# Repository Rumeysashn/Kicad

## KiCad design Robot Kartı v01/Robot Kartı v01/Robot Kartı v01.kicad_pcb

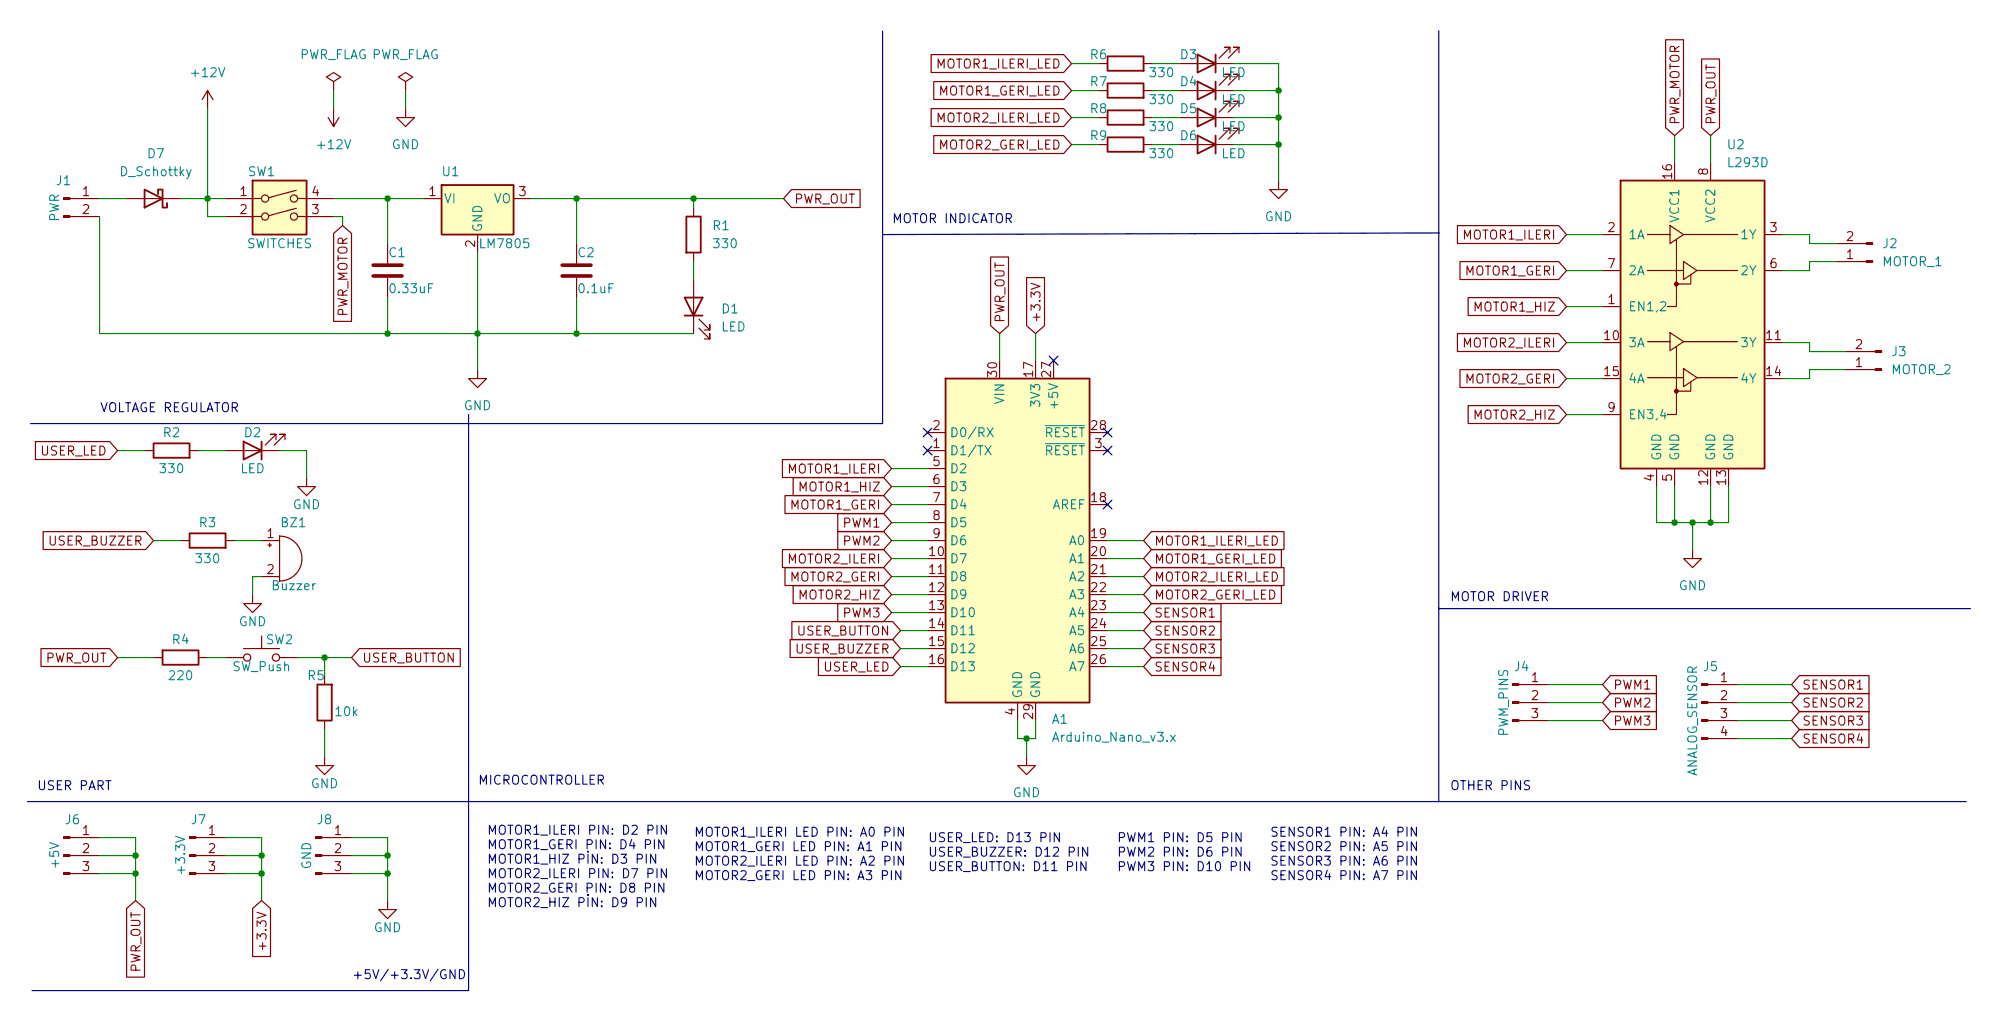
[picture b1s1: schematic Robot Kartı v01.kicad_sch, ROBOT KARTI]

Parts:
A1: Arduino_Nano_v3.x; Arduino_Nano
BZ1: Buzzer; Buzzer_12x9.5RM7.6
C1: 0.33uF; C_Disc_D3.0mm_W2.0mm_P2.50mm
C2: 0.1uF; C_Disc_D3.0mm_W2.0mm_P2.50mm
D1, D2, D3, D4, D5, D6: LED; LED_D3.0mm
D7: D_Schottky; D_A-405_P2.54mm_Vertical_AnodeUp
J1: PWR; Molex_KK-254_AE-6410-02A_1x02_P2.54mm_Vertical
J2: MOTOR_1; Molex_KK-254_AE-6410-02A_1x02_P2.54mm_Vertical
J3: MOTOR_2; Molex_KK-254_AE-6410-02A_1x02_P2.54mm_Vertical
J4: PWM_PINS; PinSocket_1x03_P2.54mm_Vertical
J5: ANALOG_SENSOR; PinSocket_1x04_P2.54mm_Vertical
J6: +5V; PinHeader_1x03_P2.54mm_Vertical
J7: +3.3V; PinHeader_1x03_P2.54mm_Vertical
J8: GND; PinHeader_1x03_P2.54mm_Vertical
R1, R2, R3, R6, R7, R8, R9: 330; R_Axial_DIN0204_L3.6mm_D1.6mm_P5.08mm_Horizontal
R4: 220; R_Axial_DIN0204_L3.6mm_D1.6mm_P5.08mm_Horizontal
R5: 10k; R_Axial_DIN0204_L3.6mm_D1.6mm_P5.08mm_Horizontal
SW1: SWITCHES; SW_DIP_SPSTx02_Slide_6.7x6.64mm_W7.62mm_P2.54mm_LowProfile
SW2: SW_Push; SW_PUSH_6mm_H4.3mm
U1: LM7805; TO-220-3_Vertical
U2: L293D; DIP-16_W7.62mm

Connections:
+3.3V: A1.17 (3V3), J7.1, J7.2, J7.3
+12V: D7.1 (K), SW1.1, SW1.2
GND: A1.4 (GND), A1.29 (GND), BZ1.2 (+), C1.2, C2.2, D1.1 (K), D2.1 (K), D3.1 (K), D4.1 (K), D5.1 (K), D6.1 (K), J1.2, J8.1, J8.2, J8.3, R5.1, U1.2 (GND), U2.4 (GND), U2.5 (GND), U2.12 (GND), U2.13 (GND)
MOTOR1_GERI: A1.7 (D4), U2.7 (2A)
MOTOR1_GERI_LED: A1.20 (A1), R7.1
MOTOR1_HIZ: A1.6 (D3), U2.1 (EN1,2)
MOTOR1_ILERI: A1.5 (D2), U2.2 (1A)
MOTOR1_ILERI_LED: A1.19 (A0), R6.1
MOTOR2_GERI: A1.11 (D8), U2.15 (4A)
MOTOR2_GERI_LED: A1.22 (A3), R9.1
MOTOR2_HIZ: A1.12 (D9), U2.9 (EN3,4)
MOTOR2_ILERI: A1.10 (D7), U2.10 (3A)
MOTOR2_ILERI_LED: A1.21 (A2), R8.1
unnamed: BZ1.1 (-), R3.2
unnamed: D1.2 (A), R1.2
unnamed: D2.2 (A), R2.2
unnamed: D3.2 (A), R6.2
unnamed: D4.2 (A), R7.2
unnamed: D5.2 (A), R8.2
unnamed: D6.2 (A), R9.2
unnamed: D7.2 (A), J1.1
unnamed: J2.1, U2.6 (2Y)
unnamed: J2.2, U2.3 (1Y)
unnamed: J3.1, U2.14 (4Y)
unnamed: J3.2, U2.11 (3Y)
unnamed: R4.1, SW2.1
unnamed: C1.1, SW1.4, U1.1 (VI)
PWM1: A1.8 (D5), J4.1
PWM2: A1.9 (D6), J4.2
PWM3: A1.13 (D10), J4.3
PWR_MOTOR: SW1.3, U2.16 (VCC1)
PWR_OUT: A1.30 (VIN), C2.1, J6.1, J6.2, J6.3, R1.1, R4.2, U1.3 (VO), U2.8 (VCC2)
SENSOR1: A1.23 (A4), J5.1
SENSOR2: A1.24 (A5), J5.2
SENSOR3: A1.25 (A6), J5.3
SENSOR4: A1.26 (A7), J5.4
USER_BUTTON: A1.14 (D11), R5.2, SW2.2
USER_BUZZER: A1.15 (D12), R3.1
USER_LED: A1.16 (D13), R2.1

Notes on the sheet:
PWM1 PIN: D5 PIN PWM2 PIN: D6 PIN PWM3 PIN: D10 PIN
USER_LED: D13 PIN USER_BUZZER: D12 PIN USER_BUTTON: D11 PIN
USER PART
+5V/+3.3V/GND
MOTOR1_ILERI PIN: D2 PIN MOTOR1_GERI PIN: D4 PIN MOTOR1_HIZ PİN: D3 PIN MOTOR2_ILERI PIN: D7 PIN MOTOR2_GERI PIN: D8 PIN MOTOR2_HIZ PİN: D9 PIN
OTHER PINS
MICROCONTROLLER
MOTOR DRIVER
MOTOR INDICATOR
MOTOR1_ILERI LED PIN: A0 PIN MOTOR1_GERI LED PIN: A1 PIN MOTOR2_ILERI LED PIN: A2 PIN MOTOR2_GERI LED PIN: A3 PIN
VOLTAGE REGULATOR
SENSOR1 PIN: A4 PIN SENSOR2 PIN: A5 PIN SENSOR3 PIN: A6 PIN SENSOR4 PIN: A7 PIN

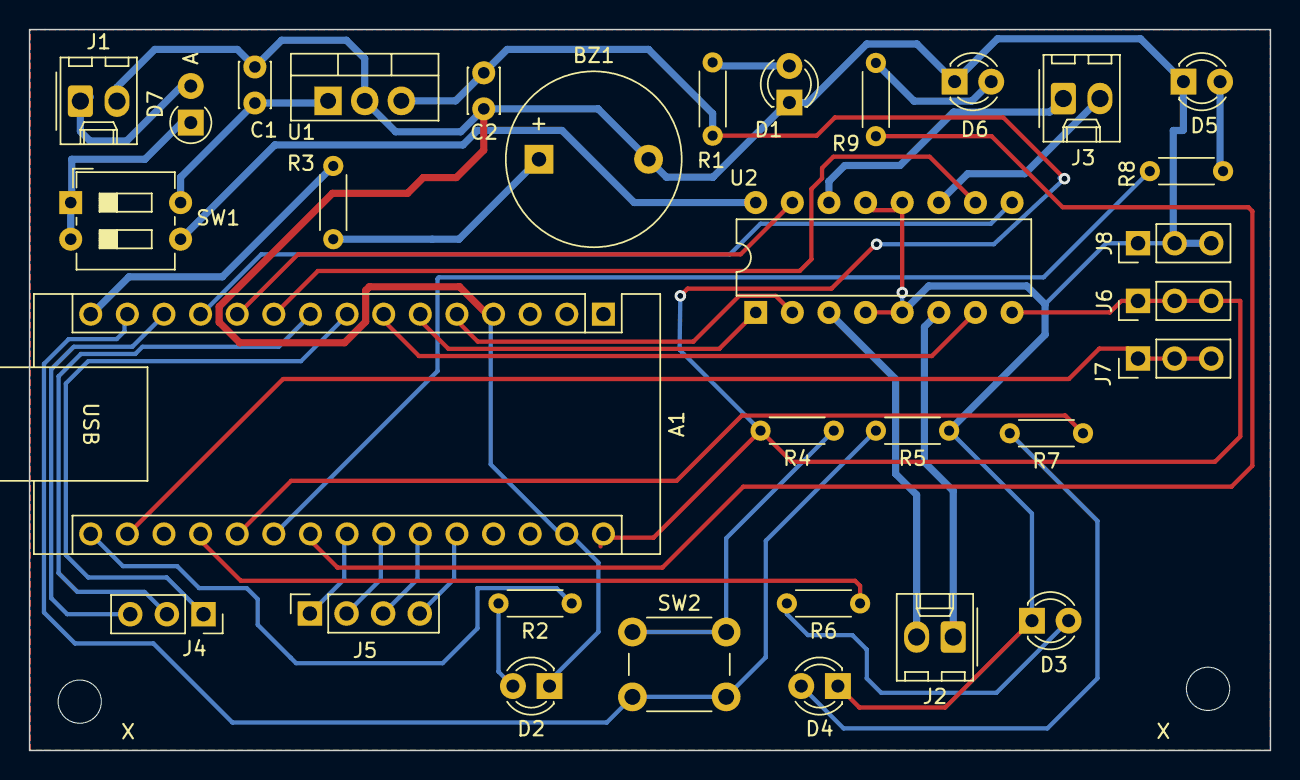
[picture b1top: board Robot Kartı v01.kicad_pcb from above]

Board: 2 copper layers, 86.1 x 50.0 mm, 34 parts (0 on the bottom side), 39 nets.

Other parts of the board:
X: MountingHole_3mm
X#2: MountingHole_3mm

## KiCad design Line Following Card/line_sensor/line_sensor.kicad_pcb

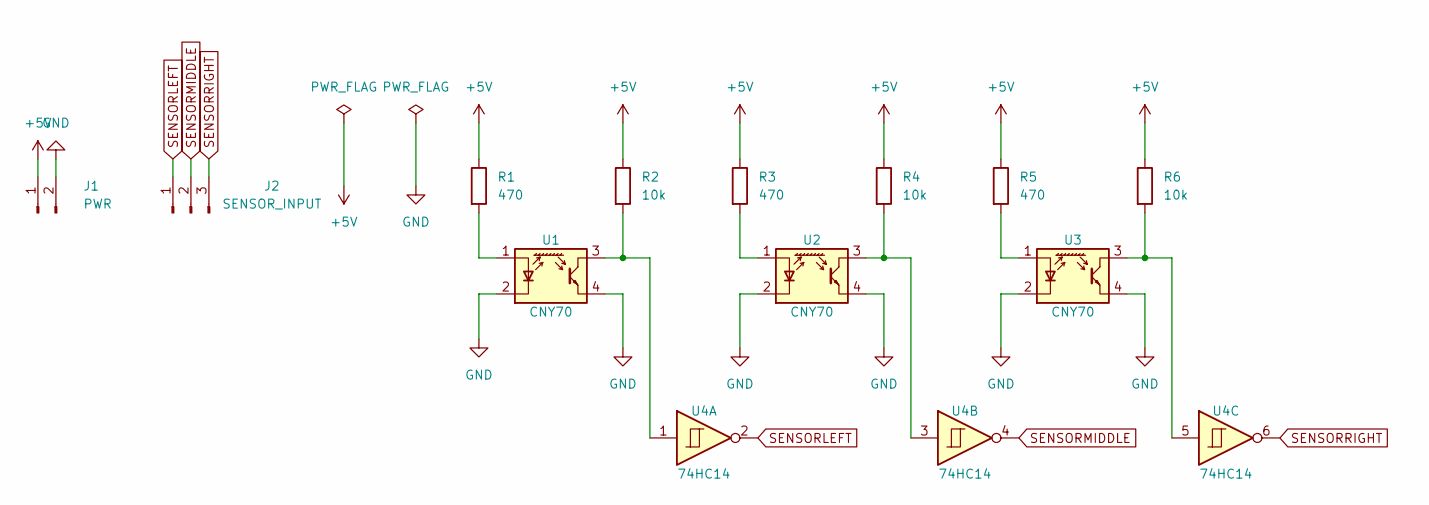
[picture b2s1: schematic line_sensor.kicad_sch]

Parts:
J1: PWR; Molex_KK-254_AE-6410-02A_1x02_P2.54mm_Vertical
J2: SENSOR_INPUT; PinHeader_1x03_P2.54mm_Vertical
R1, R3, R5: 470; R_Axial_DIN0204_L3.6mm_D1.6mm_P5.08mm_Horizontal
R2, R4, R6: 10k; R_Axial_DIN0204_L3.6mm_D1.6mm_P5.08mm_Horizontal
U1, U2, U3: CNY70; Vishay_CNY70
U4: 74HC14; DIP-14_W7.62mm

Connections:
+5V: J1.1, R1.1, R2.1, R3.1, R4.1, R5.1, R6.1, U4.14 (VCC)
GND: J1.2, U1.2 (K), U1.4 (E), U2.2 (K), U2.4 (E), U3.2 (K), U3.4 (E), U4.7 (GND)
unnamed: R1.2, U1.1 (A)
unnamed: R2.2, U1.3 (C), U4.1
unnamed: R3.2, U2.1 (A)
unnamed: R4.2, U2.3 (C), U4.3
unnamed: R5.2, U3.1 (A)
unnamed: R6.2, U3.3 (C), U4.5
SENSORLEFT: J2.1, U4.2
SENSORMIDDLE: J2.2, U4.4
SENSORRIGHT: J2.3, U4.6

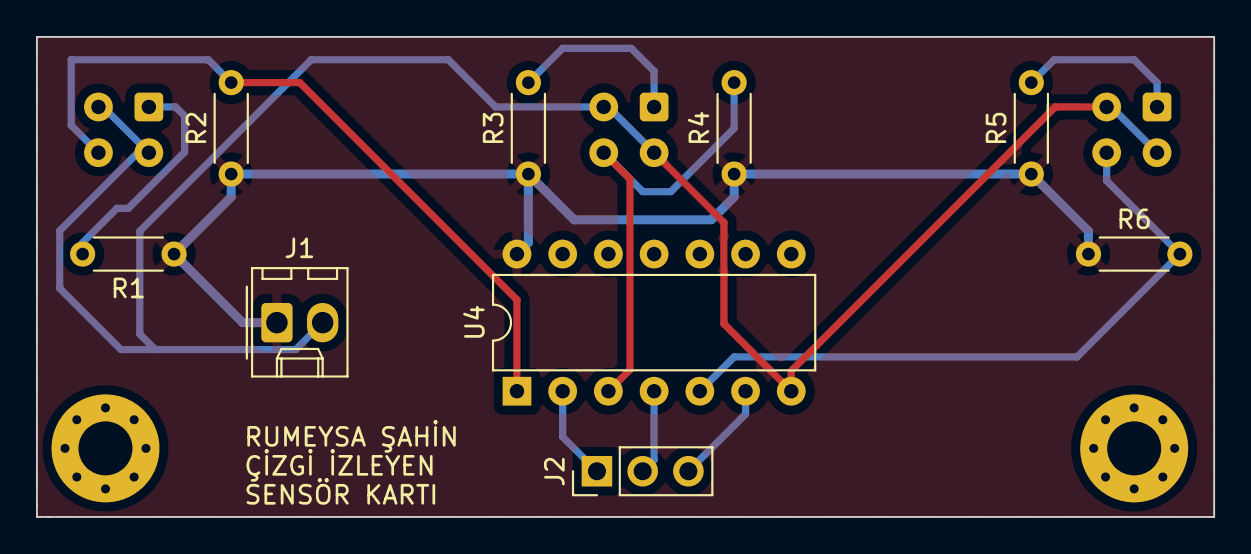
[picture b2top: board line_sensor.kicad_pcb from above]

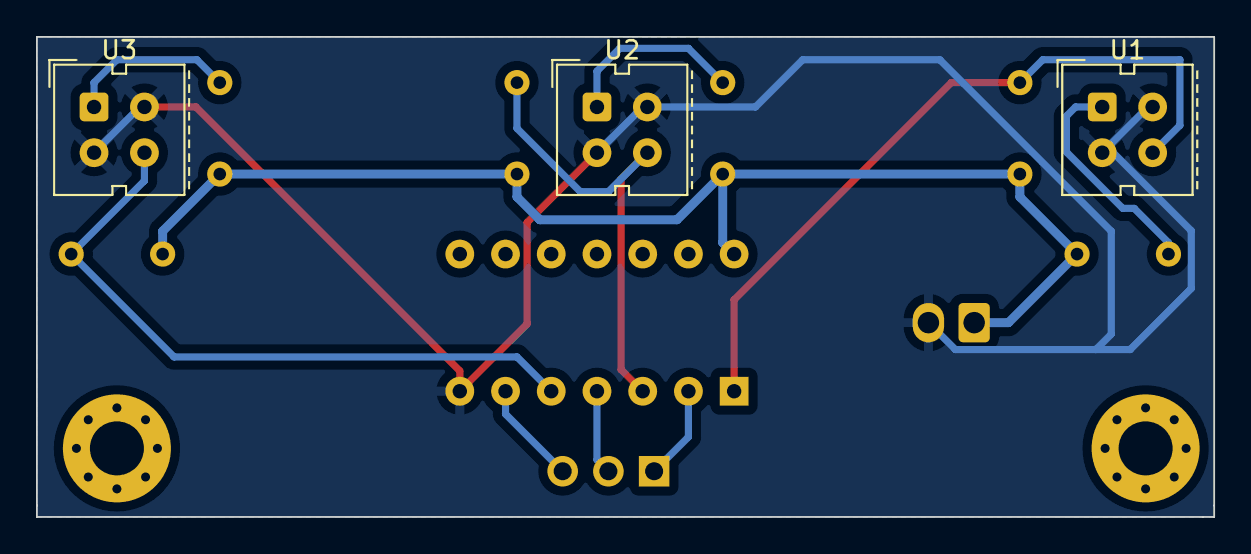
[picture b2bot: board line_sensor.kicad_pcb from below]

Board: 2 copper layers, 65.4 x 26.7 mm, 12 parts (3 on the bottom side), 11 nets.

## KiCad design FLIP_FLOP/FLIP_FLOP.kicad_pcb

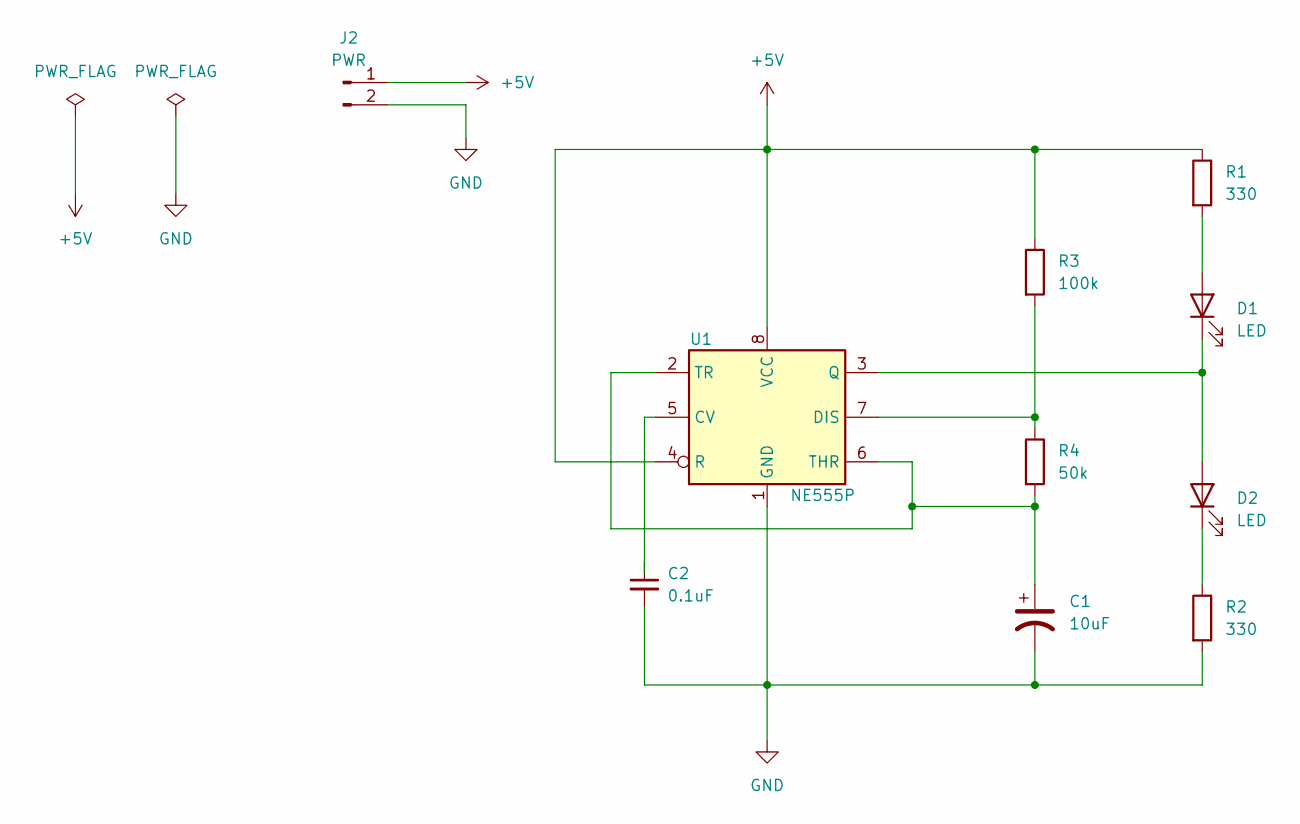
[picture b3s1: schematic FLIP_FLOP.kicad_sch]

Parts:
C1: 10uF; CP_Radial_D6.3mm_P2.50mm
C2: 0.1uF; C_Disc_D3.0mm_W1.6mm_P2.50mm
D1, D2: LED; LED_D3.0mm
J2: PWR; Molex_KK-254_AE-6410-02A_1x02_P2.54mm_Vertical
R1, R2: 330; R_Axial_DIN0204_L3.6mm_D1.6mm_P5.08mm_Horizontal
R3: 100k; R_Axial_DIN0204_L3.6mm_D1.6mm_P5.08mm_Horizontal
R4: 50k; R_Axial_DIN0204_L3.6mm_D1.6mm_P5.08mm_Horizontal
U1: NE555P; DIP-8_W7.62mm_LongPads

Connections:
+5V: J2.1, R1.1, R3.1, U1.4 (R), U1.8 (VCC)
GND: C1.2, C2.2, J2.2, R2.2, U1.1 (GND)
unnamed: D1.2 (A), R1.2
unnamed: D1.1 (K), D2.2 (A), U1.3 (Q)
unnamed: D2.1 (K), R2.1
unnamed: C2.1, U1.5 (CV)
unnamed: R3.2, R4.1, U1.7 (DIS)
unnamed: C1.1, R4.2, U1.2 (TR), U1.6 (THR)

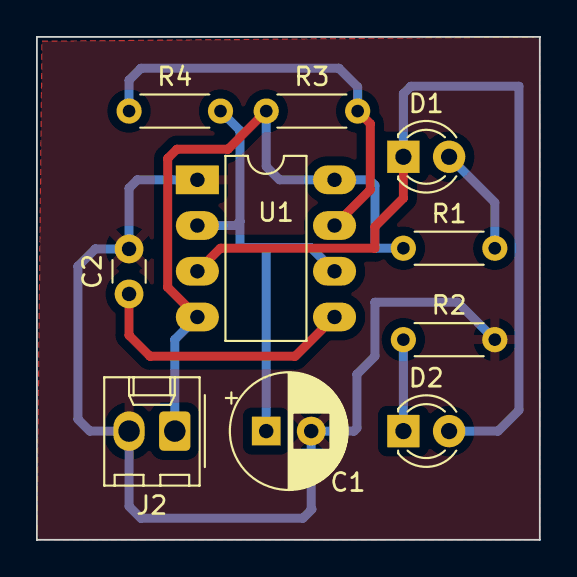
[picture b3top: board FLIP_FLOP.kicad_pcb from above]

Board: 2 copper layers, 27.9 x 27.9 mm, 10 parts (0 on the bottom side), 8 nets.

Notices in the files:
Robot Kartı v01/Robot Kartı v01/Robot Kartı v01.kicad_sch:
Kicad Open Hardware Licence
